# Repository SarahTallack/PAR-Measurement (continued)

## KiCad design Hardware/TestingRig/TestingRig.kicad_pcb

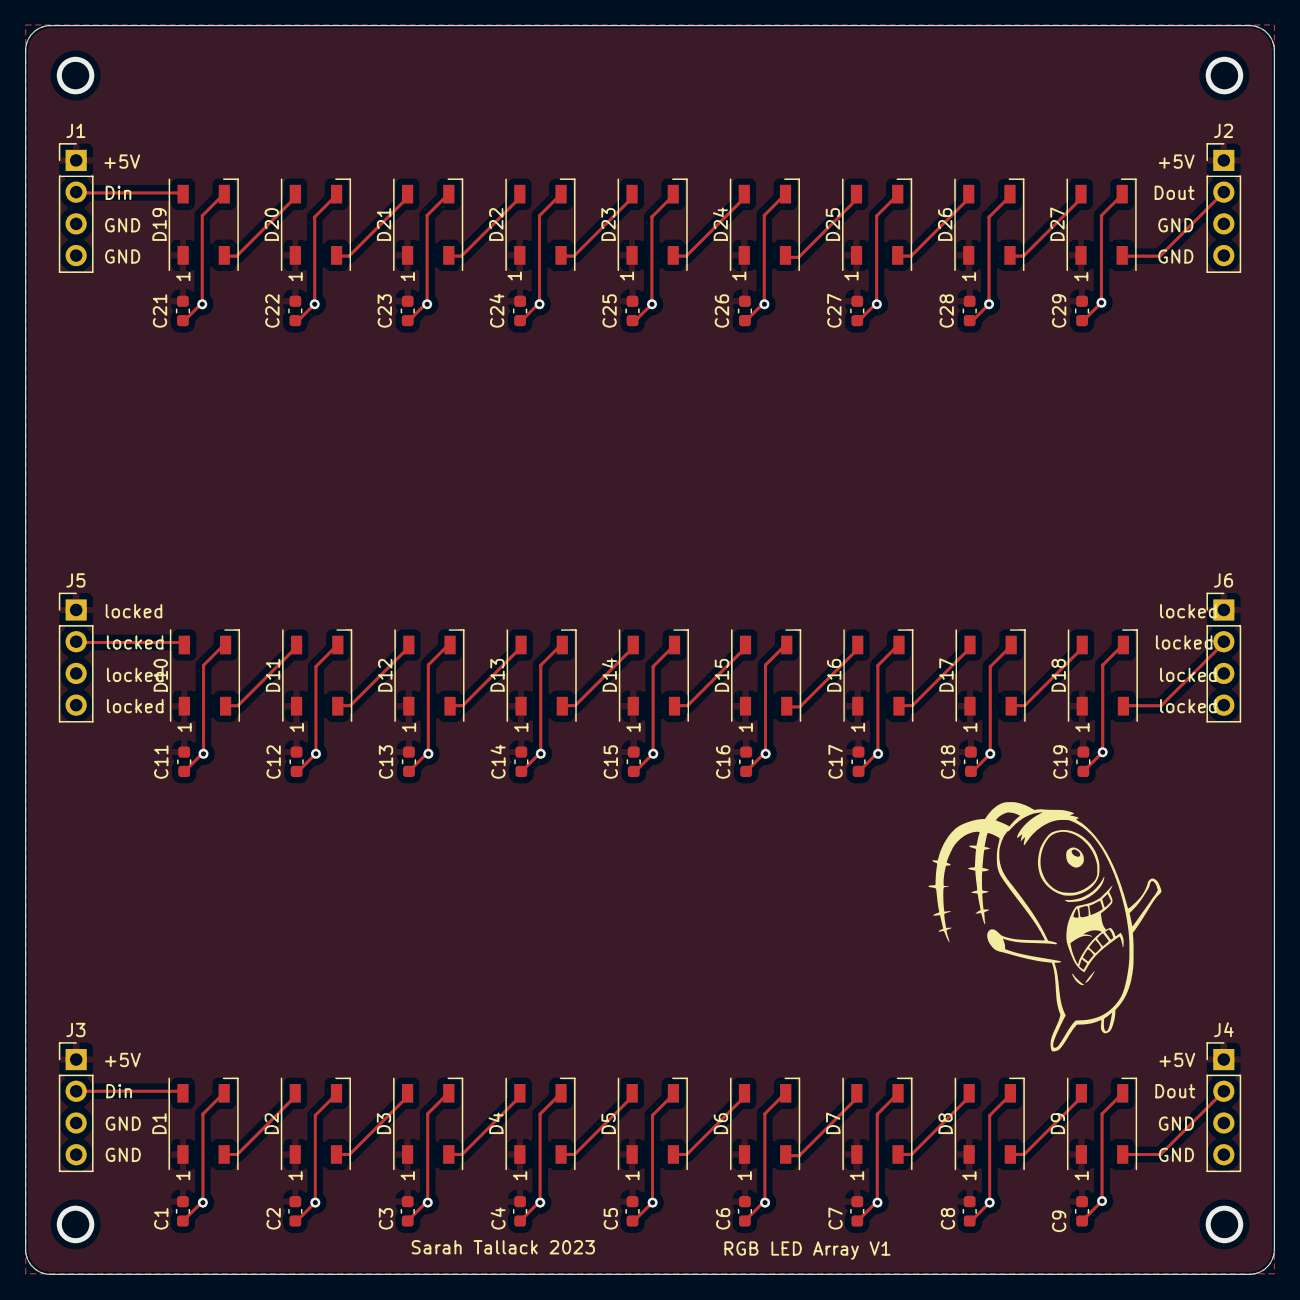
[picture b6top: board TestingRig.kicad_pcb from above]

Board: 2 copper layers, 100.0 x 100.0 mm, 60 parts (0 on the bottom side), 32 nets.

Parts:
C1, C2, C3, C4, C5, C6, C7, C8, C9, C11, C12, C13, C14, C15, C16, C17, C18, C19, C21, C22, C23, C24, C25, C26, C27, C28, C29: 100n; C_0603_1608Metric
D1, D2, D3, D4, D5, D6, D7, D8, D9, D10, D11, D12, D13, D14, D15, D16, D17, D18, D19, D20, D21, D22, D23, D24, D25, D26, D27: WS2812; LED_WS2812B_PLCC4_5.0x5.0mm_P3.2mm
J1, J2, J3, J4, J5, J6: Conn_01x04_Pin; PinHeader_1x04_P2.54mm_Vertical

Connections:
/+5V: C1.2, C2.2, C3.2, C4.2, C5.2, C6.2, C7.2, C8.2, C9.2, C11.2, C12.2, C13.2, C14.2, C15.2, C16.2, C17.2, C18.2, C19.2, C21.2, C22.2, C23.2, C24.2, C25.2, C26.2, C27.2, C28.2, C29.2, D1.1 (VDD), D2.1 (VDD), D3.1 (VDD), D4.1 (VDD), D5.1 (VDD), D6.1 (VDD), D7.1 (VDD), D8.1 (VDD), D9.1 (VDD), D10.1 (VDD), D11.1 (VDD), D12.1 (VDD), D13.1 (VDD), D14.1 (VDD), D15.1 (VDD), D16.1 (VDD), D17.1 (VDD), D18.1 (VDD), D19.1 (VDD), D20.1 (VDD), D21.1 (VDD), D22.1 (VDD), D23.1 (VDD), D24.1 (VDD), D25.1 (VDD), D26.1 (VDD), D27.1 (VDD), J1.1, J2.1, J3.1, J4.1, J5.1, J6.1
/Din1: D1.4 (DIN), J3.2
/Din10: D10.4 (DIN), J5.2
/Din19: D19.4 (DIN), J1.2
/Dout1: D1.2 (DOUT), D2.4 (DIN)
/Dout9: D9.2 (DOUT), J4.2
/Dout11: D10.2 (DOUT), D11.4 (DIN)
/Dout18: D18.2 (DOUT), J6.2
/Dout21: D19.2 (DOUT), D20.4 (DIN)
/Dout27: D27.2 (DOUT), J2.2
GND: C1.1, C2.1, C3.1, C4.1, C5.1, C6.1, C7.1, C8.1, C9.1, C11.1, C12.1, C13.1, C14.1, C15.1, C16.1, C17.1, C18.1, C19.1, C21.1, C22.1, C23.1, C24.1, C25.1, C26.1, C27.1, C28.1, C29.1, D1.3 (VSS), D2.3 (VSS), D3.3 (VSS), D4.3 (VSS), D5.3 (VSS), D6.3 (VSS), D7.3 (VSS), D8.3 (VSS), D9.3 (VSS), D10.3 (VSS), D11.3 (VSS), D12.3 (VSS), D13.3 (VSS), D14.3 (VSS), D15.3 (VSS), D16.3 (VSS), D17.3 (VSS), D18.3 (VSS), D19.3 (VSS), D20.3 (VSS), D21.3 (VSS), D22.3 (VSS), D23.3 (VSS), D24.3 (VSS), D25.3 (VSS), D26.3 (VSS), D27.3 (VSS), J1.3, J1.4, J2.3, J2.4, J3.3, J3.4, J4.3, J4.4, J5.3, J5.4, J6.3, J6.4
unnamed: D2.2 (DOUT), D3.4 (DIN)
unnamed: D3.2 (DOUT), D4.4 (DIN)
unnamed: D4.2 (DOUT), D5.4 (DIN)
unnamed: D5.2 (DOUT), D6.4 (DIN)
unnamed: D6.2 (DOUT), D7.4 (DIN)
unnamed: D7.2 (DOUT), D8.4 (DIN)
unnamed: D8.2 (DOUT), D9.4 (DIN)
unnamed: D11.2 (DOUT), D12.4 (DIN)
unnamed: D12.2 (DOUT), D13.4 (DIN)
unnamed: D13.2 (DOUT), D14.4 (DIN)
unnamed: D14.2 (DOUT), D15.4 (DIN)
unnamed: D15.2 (DOUT), D16.4 (DIN)
unnamed: D16.2 (DOUT), D17.4 (DIN)
unnamed: D17.2 (DOUT), D18.4 (DIN)
unnamed: D20.2 (DOUT), D21.4 (DIN)
unnamed: D21.2 (DOUT), D22.4 (DIN)
unnamed: D22.2 (DOUT), D23.4 (DIN)
unnamed: D23.2 (DOUT), D24.4 (DIN)
unnamed: D24.2 (DOUT), D25.4 (DIN)
unnamed: D25.2 (DOUT), D26.4 (DIN)
unnamed: D26.2 (DOUT), D27.4 (DIN)

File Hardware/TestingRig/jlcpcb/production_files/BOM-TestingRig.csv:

Comment,Designator,Footprint,LCSC
WS2812,"D1,D10,D11,D12,D13,D14,D15,D16,D17,D18,D19,D2,D20,D21,D22,D23,D24,D25,D26,D27,D3,D4,D5,D6,D7,D8,D9",LED_WS2812B_PLCC4_5.0x5.0mm_P3.2mm,C2843785
100n,"C1,C11,C12,C13,C14,C15,C16,C17,C18,C19,C2,C21,C22,C23,C24,C25,C26,C27,C28,C29,C3,C4,C5,C6,C7,C8,C9",C_0603_1608Metric,C49678

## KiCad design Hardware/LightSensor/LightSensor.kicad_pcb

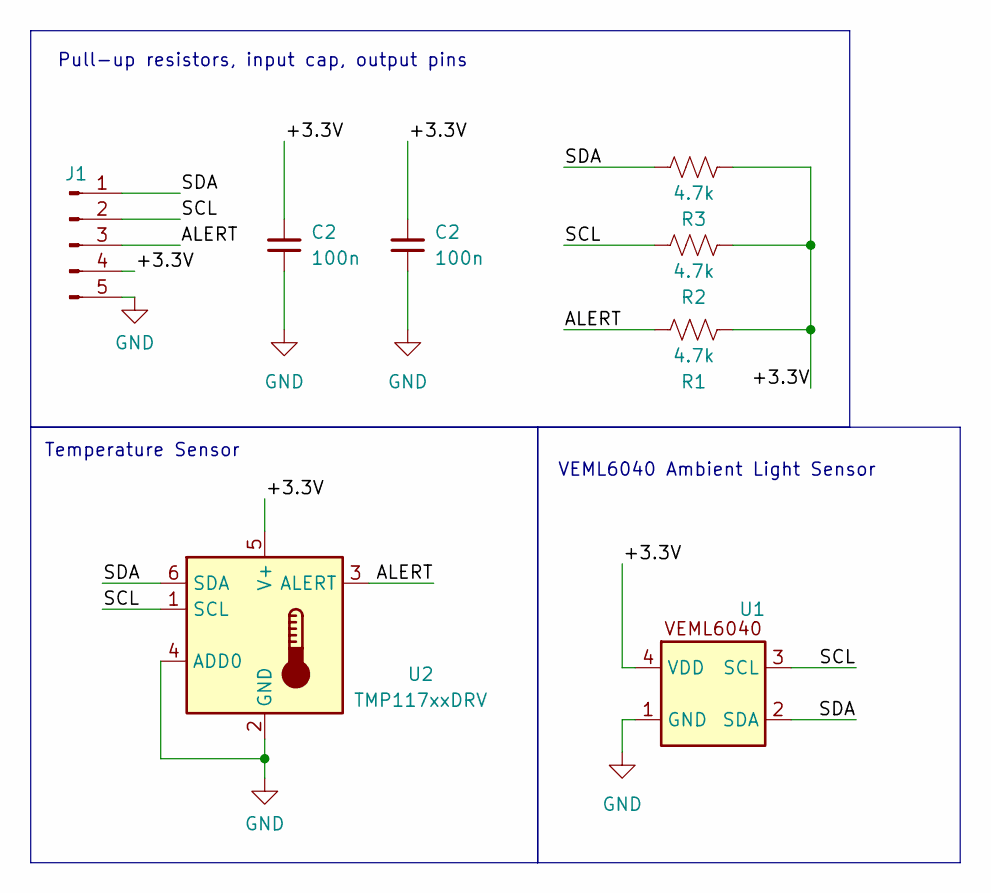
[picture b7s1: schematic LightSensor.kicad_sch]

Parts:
C2: 100n; C_0603_1608Metric; LCSC C49678
J1: Conn_01x04_Pin; PinHeader_1x05_P2.54mm_Vertical
R1, R2, R3: 4.7k; R_0603_1608Metric; LCSC C23162
U1: VEML6040; SENSOR_SMD_VEML6040A3OG; LCSC C78465
U2: TMP117xxDRV; WSON-6-1EP_2x2mm_P0.65mm_EP1x1.6mm; LCSC C699536

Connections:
/+3.3V: C2.2, J1.4, R1.1, R2.1, R3.1, U1.4 (VDD), U2.5 (V+); also elsewhere on the board
/ALERT: J1.3, R1.2, U2.3 (ALERT)
/SCL: J1.2, R2.2, U1.3 (SCL), U2.1 (SCL)
/SDA: J1.1, R3.2, U1.2 (SDA), U2.6 (SDA)
GND: C2.1, J1.5, U1.1 (GND), U2.2 (GND), U2.4 (ADD0); also elsewhere on the board

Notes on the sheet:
VEML6040 Ambient Light Sensor
Pull-up resistors, input cap, output pins
Temperature Sensor

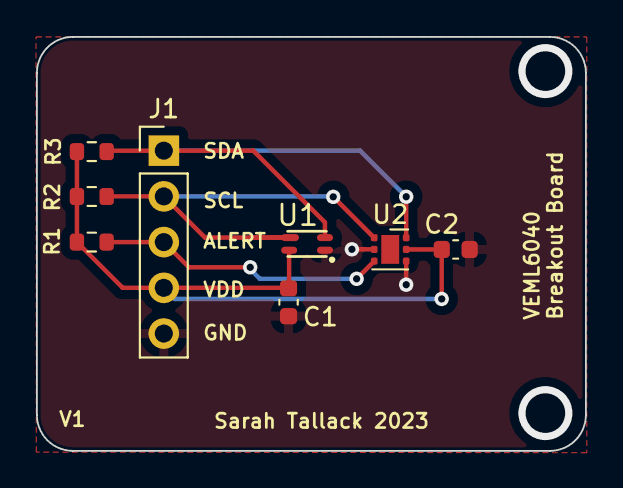
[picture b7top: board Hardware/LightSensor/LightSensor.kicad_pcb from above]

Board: 2 copper layers, 30.5 x 23.0 mm, 8 parts (0 on the bottom side), 5 nets.

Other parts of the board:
C1: 100n; C_0603_1608Metric

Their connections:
/+3.3V: C1.2; also elsewhere on the board
GND: C1.1; also elsewhere on the board

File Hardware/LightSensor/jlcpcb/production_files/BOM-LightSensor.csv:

Comment,Designator,Footprint,LCSC
4.7k,"R1,R2,R3",R_0603_1608Metric,C23162
100n,"C1,C2",C_0603_1608Metric,C49678
TMP117xxDRV,U2,WSON-6-1EP_2x2mm_P0.65mm_EP1x1.6mm,C699536
VEML6040,U1,SENSOR_SMD_VEML6040A3OG,C78465

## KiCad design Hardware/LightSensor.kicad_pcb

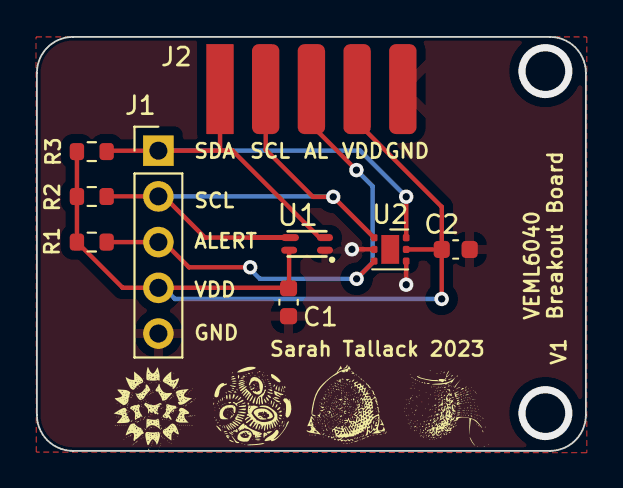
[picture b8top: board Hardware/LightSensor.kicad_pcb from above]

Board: 2 copper layers, 30.5 x 23.0 mm, 9 parts (0 on the bottom side), 5 nets.

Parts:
C1, C2: 100n; C_0603_1608Metric
J1: Conn_01x04_Pin; PinHeader_1x05_P2.54mm_Vertical
J2: Conn_01x04_Pin; conn_01x05_2.54_SMD_5mm
R1, R2, R3: 4.7k; R_0603_1608Metric
U1: VEML6040; SENSOR_SMD_VEML6040A3OG
U2: TMP117xxDRV; WSON-6-1EP_2x2mm_P0.65mm_EP1x1.6mm

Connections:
/+3.3V: C1.2, C2.2, J1.4, J2.4, R1.1, R2.1, R3.1, U1.4 (VDD), U2.5 (V+)
/ALERT: J1.3, J2.3, R1.2, U2.3 (ALERT)
/SCL: J1.2, J2.2, R2.2, U1.3 (SCL), U2.1 (SCL)
/SDA: J1.1, J2.1, R3.2, U1.2 (SDA), U2.6 (SDA)
GND: C1.1, C2.1, J1.5, J2.5, U1.1 (GND), U2.2 (GND), U2.4 (ADD0)

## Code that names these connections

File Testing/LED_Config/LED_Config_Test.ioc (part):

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Mcu.Name=STM32L476R(C-E-G)Tx
Mcu.Package=LQFP64
Mcu.UserName=STM32L476RGTx
PA0.GPIOParameters=GPIO_PuPd,GPIO_Label,GPIO_ModeDefaultEXTI
PA0.GPIO_Label=B_DOWN
PA0.GPIO_ModeDefaultEXTI=GPIO_MODE_IT_FALLING
PA0.GPIO_PuPd=GPIO_PULLUP
PA0.Signal=GPXTI0
PA10.GPIOParameters=GPIO_PuPd,GPIO_Label,GPIO_ModeDefaultEXTI
PA10.GPIO_Label=B_UP
PA10.GPIO_ModeDefaultEXTI=GPIO_MODE_IT_FALLING
PA10.GPIO_PuPd=GPIO_PULLUP
PA10.Signal=GPXTI10
PA13\ (JTMS-SWDIO).GPIOParameters=GPIO_Label
PA13\ (JTMS-SWDIO).GPIO_Label=TMS
PA13\ (JTMS-SWDIO).Mode=Serial_Wire
PA13\ (JTMS-SWDIO).Signal=SYS_JTMS-SWDIO
PA14\ (JTCK-SWCLK).GPIOParameters=GPIO_Label
PA14\ (JTCK-SWCLK).GPIO_Label=TCK
PA14\ (JTCK-SWCLK).Mode=Serial_Wire
PA14\ (JTCK-SWCLK).Signal=SYS_JTCK-SWCLK
PA2.GPIOParameters=GPIO_Speed,GPIO_PuPd,GPIO_Label,GPIO_Mode
PA2.GPIO_Label=USART_TX
PA2.GPIO_Mode=GPIO_MODE_AF_PP
PA2.GPIO_PuPd=GPIO_NOPULL
PA2.GPIO_Speed=GPIO_SPEED_FREQ_VERY_HIGH
PA2.Mode=Asynchronous
PA2.Signal=USART2_TX
PA3.GPIOParameters=GPIO_Speed,GPIO_PuPd,GPIO_Label,GPIO_Mode
PA3.GPIO_Label=USART_RX
PA3.GPIO_Mode=GPIO_MODE_AF_PP
PA3.GPIO_PuPd=GPIO_NOPULL
PA3.GPIO_Speed=GPIO_SPEED_FREQ_VERY_HIGH
PA3.Mode=Asynchronous
PA3.Signal=USART2_RX
PA5.GPIOParameters=GPIO_Label
PA5.GPIO_Label=LD2 [green Led]
PA5.Signal=GPIO_Output
PA7.GPIOParameters=GPIO_Label
PA7.GPIO_Label=LCD_D4
PA7.Signal=GPIO_Output
PA9.GPIOParameters=GPIO_Label
PA9.GPIO_Label=LCD_D7
PA9.Signal=GPIO_Output
PB10.Signal=S_TIM2_CH3
PB3\ (JTDO-TRACESWO).GPIOParameters=GPIO_Label
PB3\ (JTDO-TRACESWO).GPIO_Label=SWO
PB3\ (JTDO-TRACESWO).Signal=SYS_JTDO-SWO
PB6.GPIOParameters=GPIO_Label
PB6.GPIO_Label=LCD_D5
PB6.Signal=GPIO_Output
PB9.GPIOParameters=GPIO_Label
PB9.GPIO_Label=LCD_E
PB9.Signal=GPIO_Output
PC13.GPIOParameters=GPIO_PuPd,GPIO_Label,GPIO_ModeDefaultEXTI
PC13.GPIO_Label=B1 [Blue PushButton]
PC13.GPIO_ModeDefaultEXTI=GPIO_MODE_IT_FALLING
PC13.GPIO_PuPd=GPIO_NOPULL
PC13.Signal=GPXTI13
PC14-OSC32_IN\ (PC14).Mode=LSE-External-Oscillator
PC14-OSC32_IN\ (PC14).Signal=RCC_OSC32_IN
PC15-OSC32_OUT\ (PC15).Mode=LSE-External-Oscillator
PC15-OSC32_OUT\ (PC15).Signal=RCC_OSC32_OUT
PC7.GPIOParameters=GPIO_Label
PC7.GPIO_Label=LCD_D6
PC7.Signal=GPIO_Output
PC9.GPIOParameters=GPIO_Label
PC9.GPIO_Label=LCD_RS
PC9.Signal=GPIO_Output
PH0-OSC_IN\ (PH0).Signal=RCC_OSC_IN
PH1-OSC_OUT\ (PH1).Signal=RCC_OSC_OUT
RCC.HSE_VALUE=8000000
RCC.SYSCLKFreq_VALUE=80000000
RCC.SYSCLKSource=RCC_SYSCLKSOURCE_PLLCLK
board=NUCLEO-L476RG
boardIOC=true

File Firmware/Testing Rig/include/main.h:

/* USER CODE BEGIN Header */
/**
  ******************************************************************************
  * @file           : main.h
  * @brief          : Header for main.c file.
  *                   This file contains the common defines of the application.
  ******************************************************************************
  * @attention
  *
  * Copyright (c) 2024 STMicroelectronics.
  * All rights reserved.
  *
  * This software is licensed under terms that can be found in the LICENSE file
  * in the root directory of this software component.
  * If no LICENSE file comes with this software, it is provided AS-IS.
  *
  ******************************************************************************
  */
/* USER CODE END Header */

/* Define to prevent recursive inclusion -------------------------------------*/
#ifndef __MAIN_H
#define __MAIN_H

#ifdef __cplusplus
extern "C" {
#endif

/* Includes ------------------------------------------------------------------*/
#include "stm32l4xx_hal.h"

/* Private includes ----------------------------------------------------------*/
/* USER CODE BEGIN Includes */

/* USER CODE END Includes */

/* Exported types ------------------------------------------------------------*/
/* USER CODE BEGIN ET */

/* USER CODE END ET */

/* Exported constants --------------------------------------------------------*/
/* USER CODE BEGIN EC */

/* USER CODE END EC */

/* Exported macro ------------------------------------------------------------*/
/* USER CODE BEGIN EM */

/* USER CODE END EM */

/* Exported functions prototypes ---------------------------------------------*/
void Error_Handler(void);

/* USER CODE BEGIN EFP */

/* USER CODE END EFP */

/* Private defines -----------------------------------------------------------*/
#define B1_Pin GPIO_PIN_13
#define B1_GPIO_Port GPIOC
#define B1_EXTI_IRQn EXTI15_10_IRQn
#define USART_TX_Pin GPIO_PIN_2
#define USART_TX_GPIO_Port GPIOA
#define USART_RX_Pin GPIO_PIN_3
#define USART_RX_GPIO_Port GPIOA
#define LD2_Pin GPIO_PIN_5
#define LD2_GPIO_Port GPIOA
#define LCD_D7_Pin GPIO_PIN_7
#define LCD_D7_GPIO_Port GPIOA
#define CURRENT_SENSOR_Pin GPIO_PIN_4
#define CURRENT_SENSOR_GPIO_Port GPIOC
#define LCD_RS_Pin GPIO_PIN_10
#define LCD_RS_GPIO_Port GPIOB
#define LED_CONTROL_Pin GPIO_PIN_11
#define LED_CONTROL_GPIO_Port GPIOB
#define SCL_MASTER_Pin GPIO_PIN_13
#define SCL_MASTER_GPIO_Port GPIOB
#define SDA_MASTER_Pin GPIO_PIN_14
#define SDA_MASTER_GPIO_Port GPIOB
#define I2C_RESET_Pin GPIO_PIN_15
#define I2C_RESET_GPIO_Port GPIOB
#define LCD_D5_Pin GPIO_PIN_7
#define LCD_D5_GPIO_Port GPIOC
#define LCD_E_Pin GPIO_PIN_8
#define LCD_E_GPIO_Port GPIOA
#define LCD_D4_Pin GPIO_PIN_9
#define LCD_D4_GPIO_Port GPIOA
#define TMS_Pin GPIO_PIN_13
#define TMS_GPIO_Port GPIOA
#define TCK_Pin GPIO_PIN_14
#define TCK_GPIO_Port GPIOA
#define UB2_Pin GPIO_PIN_10
#define UB2_GPIO_Port GPIOC
#define UB1_Pin GPIO_PIN_12
#define UB1_GPIO_Port GPIOC
#define SWO_Pin GPIO_PIN_3
#define SWO_GPIO_Port GPIOB
#define LCD_D6_Pin GPIO_PIN_6
#define LCD_D6_GPIO_Port GPIOB
#define UB3_Pin GPIO_PIN_7
#define UB3_GPIO_Port GPIOB

/* USER CODE BEGIN Private defines */

/* USER CODE END Private defines */

#ifdef __cplusplus
}
#endif

#endif /* __MAIN_H */

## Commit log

2023-07-30 Literature Review
2023-07-30 message
2023-10-09 data
2023-10-10 testing data
2023-10-11 test 2 data
2023-10-11 distance tests
2023-10-12 testing
2023-10-16 SENSOR STUFF
2023-10-17 pcb stuffs i guess
2023-10-24 testing stuff
2023-10-26 testing much
2023-10-30 formatting repo
2024-04-22 last
2025-02-02 2024WorkUpdate
